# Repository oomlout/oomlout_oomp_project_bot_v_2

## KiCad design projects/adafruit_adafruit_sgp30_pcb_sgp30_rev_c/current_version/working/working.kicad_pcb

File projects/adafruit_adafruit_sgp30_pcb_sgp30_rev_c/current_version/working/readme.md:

# adafruit_sgp30_pcb
 
## summary 
* id: adafruit_adafruit_sgp30_pcb_sgp30_rev_c
* user: adafruit
* name: adafruit_sgp30_pcb
* board: sgp30_rev_c
* repo: https://github.com/adafruit/Adafruit-SGP30-PCB

* src_file_repo_sch: 
* src_file_repo_sch_link: https://github.com/adafruit/Adafruit-SGP30-PCB/tree/master/
* full details link: https://github.com/oomlout/oomlout_oomp_project_bot_v_2/tree/main/projects/adafruit_adafruit_sgp30_pcb_sgp30_rev_c/current_version/working  

## schematic  
  
[schematic (pdf)](working_schematic.pdf) 

## pcb  

[board (pdf)](working.pdf)  

## working_bom
| Id | Designator | Footprint | Quantity | Designation | Supplier and ref |  | None | 
| --- | --- | --- | --- | --- | --- | --- | --- | 
| 1 | FID4,FID3 | FIDUCIAL_1MM | 2 | FIDUCIAL_1MM |  |  | [''] | 
| 2 | CONN4,CONN3 | JST_SH4 | 2 | STEMMA_I2C_QT |  |  | [''] | 
| 3 | C5,C4 | 0805-NO | 2 | 10uF |  |  | [''] | 
| 4 | U1 | SOT23-5 | 1 | MIC5225-1.8V |  |  | [''] | 
| 5 | U$2 | SGP30 | 1 | SGP30 |  |  | [''] | 
| 6 | U$29,U$31,U$32,U$28 | MOUNTINGHOLE_2.5_PLATED | 4 | MOUNTINGHOLE2.5 |  |  | [''] | 
| 7 | D1 | CHIPLED_0603_NOOUTLINE | 1 | GREEN |  |  | [''] | 
| 8 | Q2 | SOT363 | 1 | BSS138 |  |  | [''] | 
| 9 | U$34 | ADAFRUIT_3.5MM | 1 |  |  |  | [''] | 
| 10 | C6 | 0603-NO | 1 | 0.1uF |  |  | [''] | 
| 11 | R3 | RESPACK_4X0603 | 1 | 10K |  |  | [''] | 
| 12 | JP3 | 1X05_ROUND_70 | 1 |  |  |  | [''] | 
| 13 | R2 | 0603-NO | 1 | 10K |  |  | [''] | 
| 14 | U$37,U$36 | STEMMAQT | 2 |  |  |  | [''] | 
| 15 | U$35 | PCBFEAT-REV-040 | 1 |  |  |  | [''] | 

## bom_schematic
| Ref | Qnty | Value | Cmp name | Footprint | Description | Vendor | DNP | 
| --- | --- | --- | --- | --- | --- | --- | --- | 
| C4, C5 | 2 | 10uF | CAP_CERAMIC0805-NOOUTLINE | working:0805-NO |  |  |  | 
| C6 | 1 | 0.1uF | CAP_CERAMIC0603_NO | working:0603-NO |  |  |  | 
| CONN3, CONN4 | 2 | STEMMA_I2C_QT | STEMMA_I2C_QT | working:JST_SH4 |  |  |  | 
| D1 | 1 | GREEN | LED0603_NOOUTLINE | working:CHIPLED_0603_NOOUTLINE |  |  |  | 
| FID3, FID4 | 2 | FIDUCIAL_1MM | FIDUCIAL_1MM | working:FIDUCIAL_1MM |  |  |  | 
| JP3 | 1 | HEADER-1X570MIL | HEADER-1X570MIL | working:1X05_ROUND_70 |  |  |  | 
| Q2 | 1 | BSS138 | MOSFET-N_DUAL | working:SOT363 |  |  |  | 
| R2 | 1 | 10K | RESISTOR_0603_NOOUT | working:0603-NO |  |  |  | 
| R3 | 1 | 10K | RESISTOR_4PACK | working:RESPACK_4X0603 |  |  |  | 
| U1 | 1 | MIC5225-1.8V | VREG_SOT23-5 | working:SOT23-5 |  |  |  | 
| U$2 | 1 | SGP30 | SGP30 | working:SGP30 |  |  |  | 
| U$28, U$29, U$31, U$32 | 4 | MOUNTINGHOLE2.5 | MOUNTINGHOLE2.5 | working:MOUNTINGHOLE_2.5_PLATED |  |  |  | 

## mounting_holes
| x | y | package | value | ref | size | 
| --- | --- | --- | --- | --- | --- | 
| 0.0 | 12.7 | MOUNTINGHOLE_2.5_PLATED | MOUNTINGHOLE2.5 | U$28 | m3 | 
| 20.32 | 12.7 | MOUNTINGHOLE_2.5_PLATED | MOUNTINGHOLE2.5 | U$29 | m3 | 
| 0.0 | 0.0 | MOUNTINGHOLE_2.5_PLATED | MOUNTINGHOLE2.5 | U$31 | m3 | 
| 20.32 | 0.0 | MOUNTINGHOLE_2.5_PLATED | MOUNTINGHOLE2.5 | U$32 | m3 |

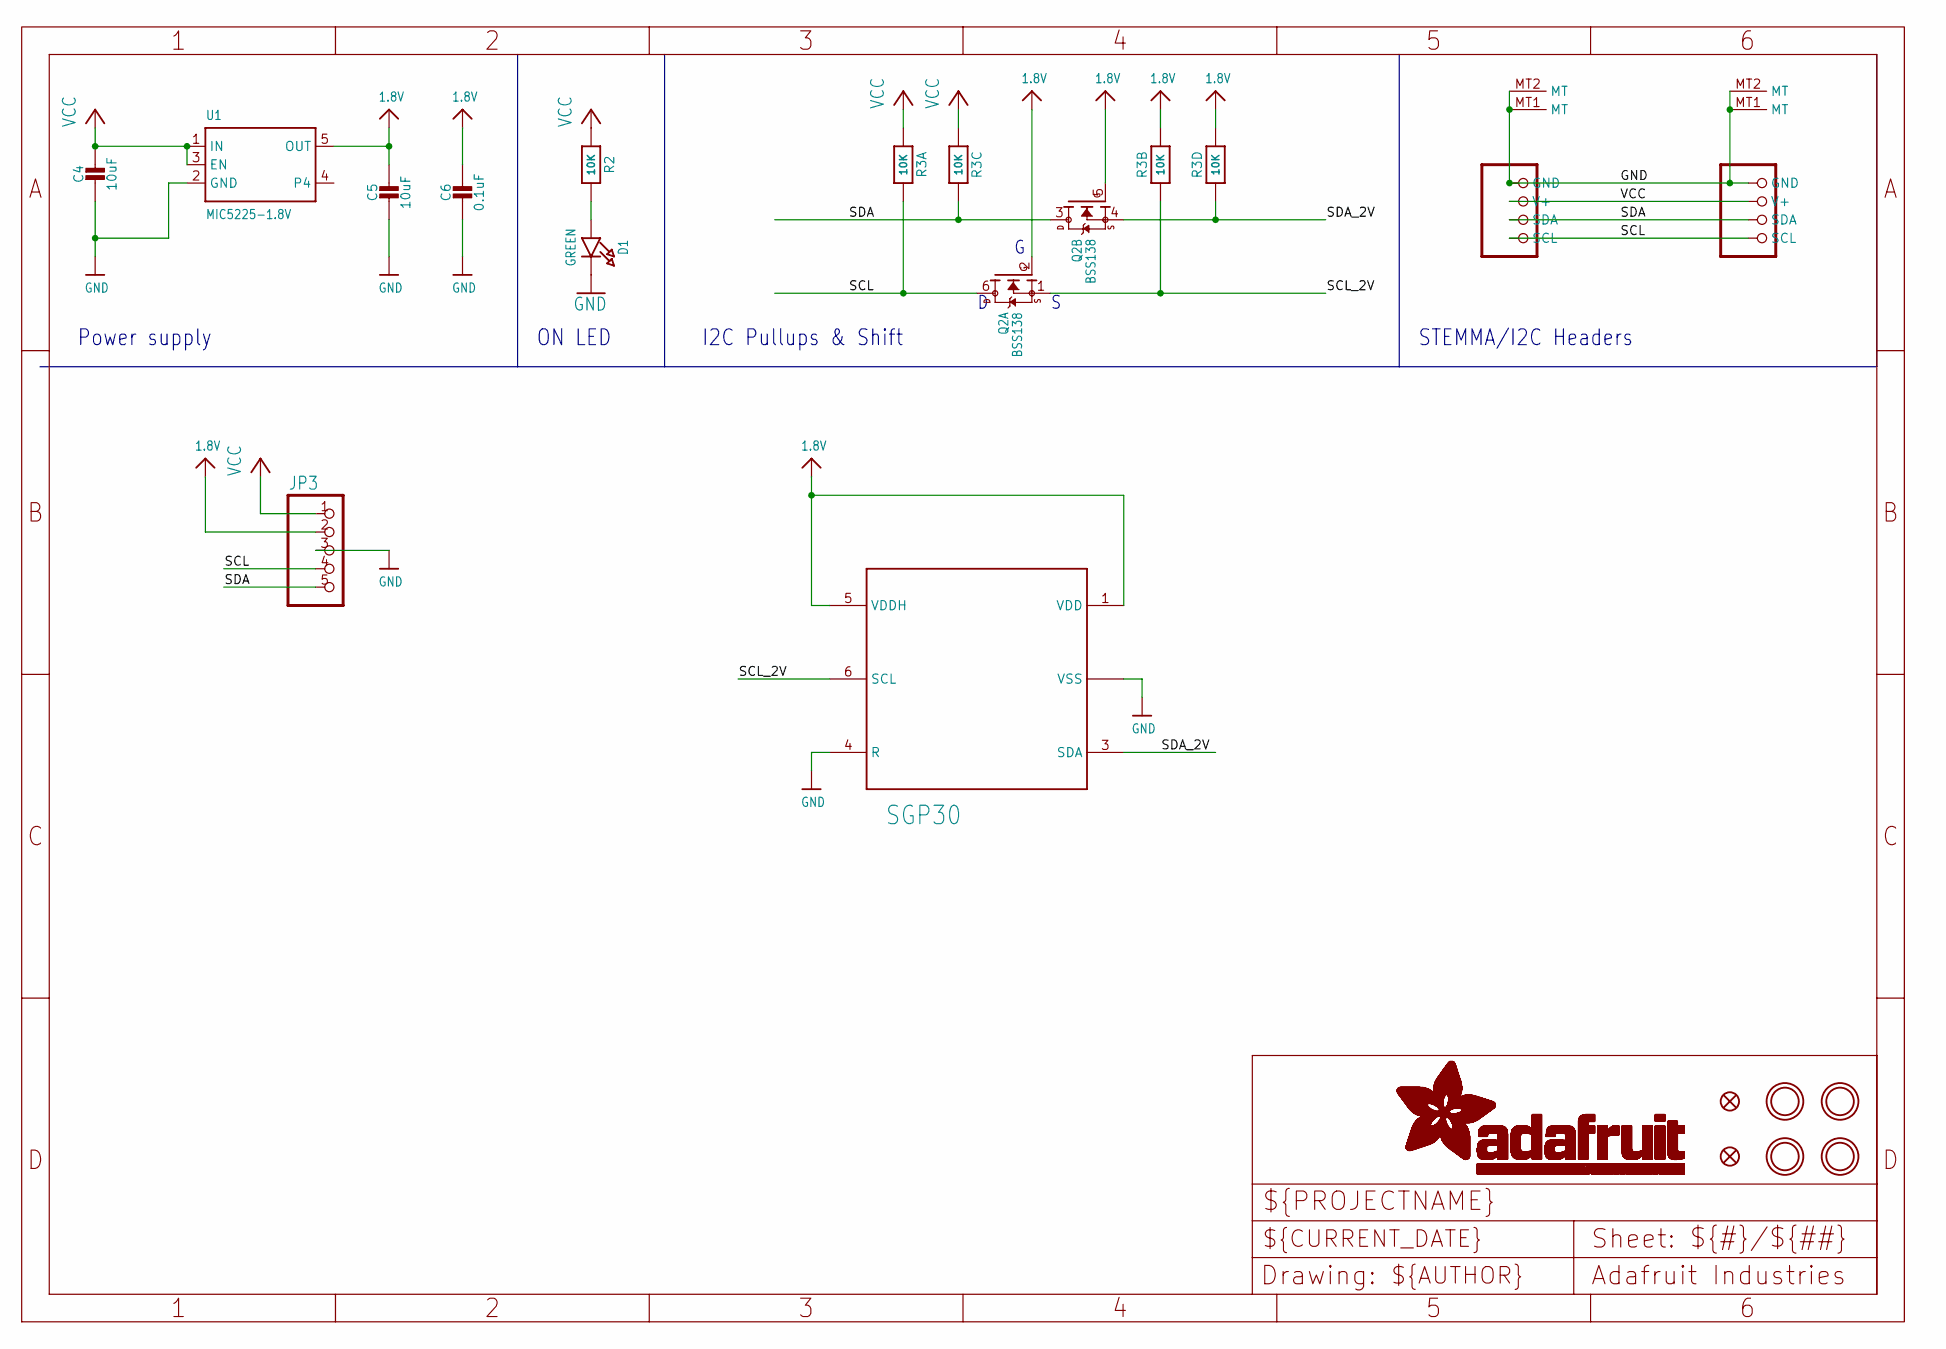
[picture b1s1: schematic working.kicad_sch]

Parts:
C4, C5: 10uF; 0805-NO
C6: 0.1uF; 0603-NO
CONN3, CONN4: STEMMA_I2C_QT; JST_SH4
D1: GREEN; CHIPLED_0603_NOOUTLINE
FID3, FID4: FIDUCIAL_1MM
JP3: HEADER-1X570MIL; 1X05_ROUND_70
Q2: BSS138; SOT363
R2: 10K; 0603-NO
R3: 10K; RESPACK_4X0603
U1: MIC5225-1.8V; SOT23-5
U$2: SGP30
U$28, U$29, U$31, U$32: MOUNTINGHOLE2.5; MOUNTINGHOLE_2.5_PLATED

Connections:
1.8V: C5.1, C6.1, JP3.2, Q2.2 (G), Q2.5 (G), R3.2 (1), R3.4 (1), U1.5 (OUT), U$2.1 (VDD), U$2.5 (VDDH)
GND: C4.2, C5.2, C6.2, CONN3.1 (GND), CONN3.MT1 (MT), CONN3.MT2 (MT), CONN4.1 (GND), CONN4.MT1 (MT), CONN4.MT2 (MT), D1.C, JP3.3, U1.2 (GND), U$2.2 (VSS), U$2.4 (R), U$2.P$7 (VSS)
unnamed: D1.A, R2.2
SCL: CONN3.4 (SCL), CONN4.4 (SCL), JP3.4, Q2.6 (D), R3.8 (2)
SCL_2V: Q2.1 (S), R3.7 (2), U$2.6 (SCL)
SDA: CONN3.3 (SDA), CONN4.3 (SDA), JP3.5, Q2.3 (D), R3.6 (2)
SDA_2V: Q2.4 (S), R3.5 (2), U$2.3 (SDA)
VCC: C4.1, CONN3.2 (V+), CONN4.2 (V+), JP3.1, R2.1, R3.1, R3.3 (1), U1.1 (IN), U1.3 (EN)

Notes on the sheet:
STEMMA/I2C Headers
ON LED
Power supply
I2C Pullups & Shift

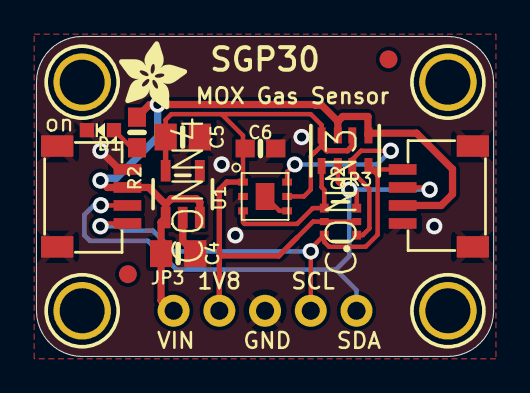
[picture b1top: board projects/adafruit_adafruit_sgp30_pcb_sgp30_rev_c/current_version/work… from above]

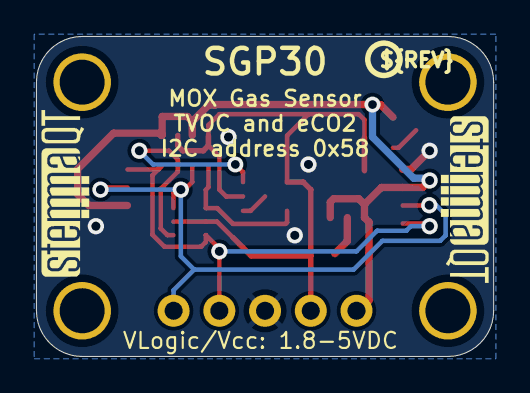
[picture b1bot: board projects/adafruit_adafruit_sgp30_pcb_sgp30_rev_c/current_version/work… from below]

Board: 2 copper layers, 25.4 x 17.8 mm, 22 parts (3 on the bottom side), 8 nets.

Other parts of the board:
U$34: ADAFRUIT_3.5MM
U$35: PCBFEAT-REV-040
U$36, U$37: STEMMAQT

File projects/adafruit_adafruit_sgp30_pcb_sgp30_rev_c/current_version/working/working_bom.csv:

"Id";"Designator";"Footprint";"Quantity";"Designation";"Supplier and ref";
1;"FID4,FID3";"FIDUCIAL_1MM";2;"FIDUCIAL_1MM";;;
2;"CONN4,CONN3";"JST_SH4";2;"STEMMA_I2C_QT";;;
3;"C5,C4";"0805-NO";2;"10uF";;;
4;"U1";"SOT23-5";1;"MIC5225-1.8V";;;
5;"U$2";"SGP30";1;"SGP30";;;
6;"U$29,U$31,U$32,U$28";"MOUNTINGHOLE_2.5_PLATED";4;"MOUNTINGHOLE2.5";;;
7;"D1";"CHIPLED_0603_NOOUTLINE";1;"GREEN";;;
8;"Q2";"SOT363";1;"BSS138";;;
9;"U$34";"ADAFRUIT_3.5MM";1;"";;;
10;"C6";"0603-NO";1;"0.1uF";;;
11;"R3";"RESPACK_4X0603";1;"10K";;;
12;"JP3";"1X05_ROUND_70";1;"";;;
13;"R2";"0603-NO";1;"10K";;;
14;"U$37,U$36";"STEMMAQT";2;"";;;
15;"U$35";"PCBFEAT-REV-040";1;"";;;

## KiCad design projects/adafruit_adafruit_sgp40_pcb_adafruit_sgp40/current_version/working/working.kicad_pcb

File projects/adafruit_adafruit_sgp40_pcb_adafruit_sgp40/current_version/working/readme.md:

# adafruit_sgp40_pcb
 
## summary 
* id: adafruit_adafruit_sgp40_pcb_adafruit_sgp40
* user: adafruit
* name: adafruit_sgp40_pcb
* board: adafruit_sgp40
* repo: https://github.com/adafruit/Adafruit-SGP40-PCB

* src_file_repo_sch: 
* src_file_repo_sch_link: https://github.com/adafruit/Adafruit-SGP40-PCB/tree/main/
* full details link: https://github.com/oomlout/oomlout_oomp_project_bot_v_2/tree/main/projects/adafruit_adafruit_sgp40_pcb_adafruit_sgp40/current_version/working  

## schematic  
  
[schematic (pdf)](working_schematic.pdf) 

## pcb  

[board (pdf)](working.pdf)  

## working_bom
| Id | Designator | Footprint | Quantity | Designation | Supplier and ref |  | None | 
| --- | --- | --- | --- | --- | --- | --- | --- | 
| 1 | D1 | CHIPLED_0603_NOOUTLINE | 1 | Green |  |  | [''] | 
| 2 | R3 | RESPACK_4X0603 | 1 | 10K |  |  | [''] | 
| 3 | R2 | 0603-NO | 1 | 10K |  |  | [''] | 
| 4 | CONN4,CONN3 | JST_SH4 | 2 | STEMMA_I2C_QT |  |  | [''] | 
| 5 | U$28,U$32,U$31,U$29 | MOUNTINGHOLE_2.5_PLATED | 4 | MOUNTINGHOLE2.5 |  |  | [''] | 
| 6 | U1 | SOT23-5 | 1 | AP2112-3.3K |  |  | [''] | 
| 7 | U$34 | ADAFRUIT_3.5MM | 1 |  |  |  | [''] | 
| 8 | Q2 | SOT363 | 1 | BSS138 |  |  | [''] | 
| 9 | JP3 | 1X05_ROUND_70 | 1 |  |  |  | [''] | 
| 10 | FID3,FID4 | FIDUCIAL_1MM | 2 | FIDUCIAL_1MM |  |  | [''] | 
| 11 | C6 | 0603-NO | 1 | 0.1uF |  |  | [''] | 
| 12 | C5,C4 | 0805-NO | 2 | 10uF |  |  | [''] | 
| 13 | X1 | SGP30 | 1 | SGP40 |  |  | [''] | 
| 14 | R1 | 0603-NO | 1 | 4.7ohm |  |  | [''] | 
| 15 | U$37,U$36 | STEMMAQT | 2 |  |  |  | [''] | 
| 16 | U$35 | PCBFEAT-REV-040 | 1 |  |  |  | [''] | 

## bom_schematic
| Ref | Qnty | Value | Cmp name | Footprint | Description | Vendor | DNP | 
| --- | --- | --- | --- | --- | --- | --- | --- | 
| C4, C5 | 2 | 10uF | CAP_CERAMIC0805-NOOUTLINE | working:0805-NO |  |  |  | 
| C6 | 1 | 0.1uF | CAP_CERAMIC0603_NO | working:0603-NO |  |  |  | 
| CONN3, CONN4 | 2 | STEMMA_I2C_QT | STEMMA_I2C_QT | working:JST_SH4 |  |  |  | 
| D1 | 1 | Green | LED0603_NOOUTLINE | working:CHIPLED_0603_NOOUTLINE |  |  |  | 
| FID3, FID4 | 2 | FIDUCIAL_1MM | FIDUCIAL_1MM | working:FIDUCIAL_1MM |  |  |  | 
| JP3 | 1 | HEADER-1X570MIL | HEADER-1X570MIL | working:1X05_ROUND_70 |  |  |  | 
| Q2 | 1 | BSS138 | MOSFET-N_DUAL | working:SOT363 |  |  |  | 
| R1 | 1 | 4.7ohm | RESISTOR_0603_NOOUT | working:0603-NO |  |  |  | 
| R2 | 1 | 10K | RESISTOR_0603_NOOUT | working:0603-NO |  |  |  | 
| R3 | 1 | 10K | RESISTOR_4PACK | working:RESPACK_4X0603 |  |  |  | 
| U1 | 1 | AP2112-3.3K | VREG_SOT23-5 | working:SOT23-5 |  |  |  | 
| U$28, U$29, U$31, U$32 | 4 | MOUNTINGHOLE2.5 | MOUNTINGHOLE2.5 | working:MOUNTINGHOLE_2.5_PLATED |  |  |  | 
| X1 | 1 | SGP30 | SGP30 | working:SGP30 |  |  |  | 

## mounting_holes
| x | y | package | value | ref | size | 
| --- | --- | --- | --- | --- | --- | 
| 0.0 | 12.7 | MOUNTINGHOLE_2.5_PLATED | MOUNTINGHOLE2.5 | U$28 | m3 | 
| 20.32 | 12.7 | MOUNTINGHOLE_2.5_PLATED | MOUNTINGHOLE2.5 | U$29 | m3 | 
| 0.0 | 0.0 | MOUNTINGHOLE_2.5_PLATED | MOUNTINGHOLE2.5 | U$31 | m3 | 
| 20.32 | 0.0 | MOUNTINGHOLE_2.5_PLATED | MOUNTINGHOLE2.5 | U$32 | m3 |

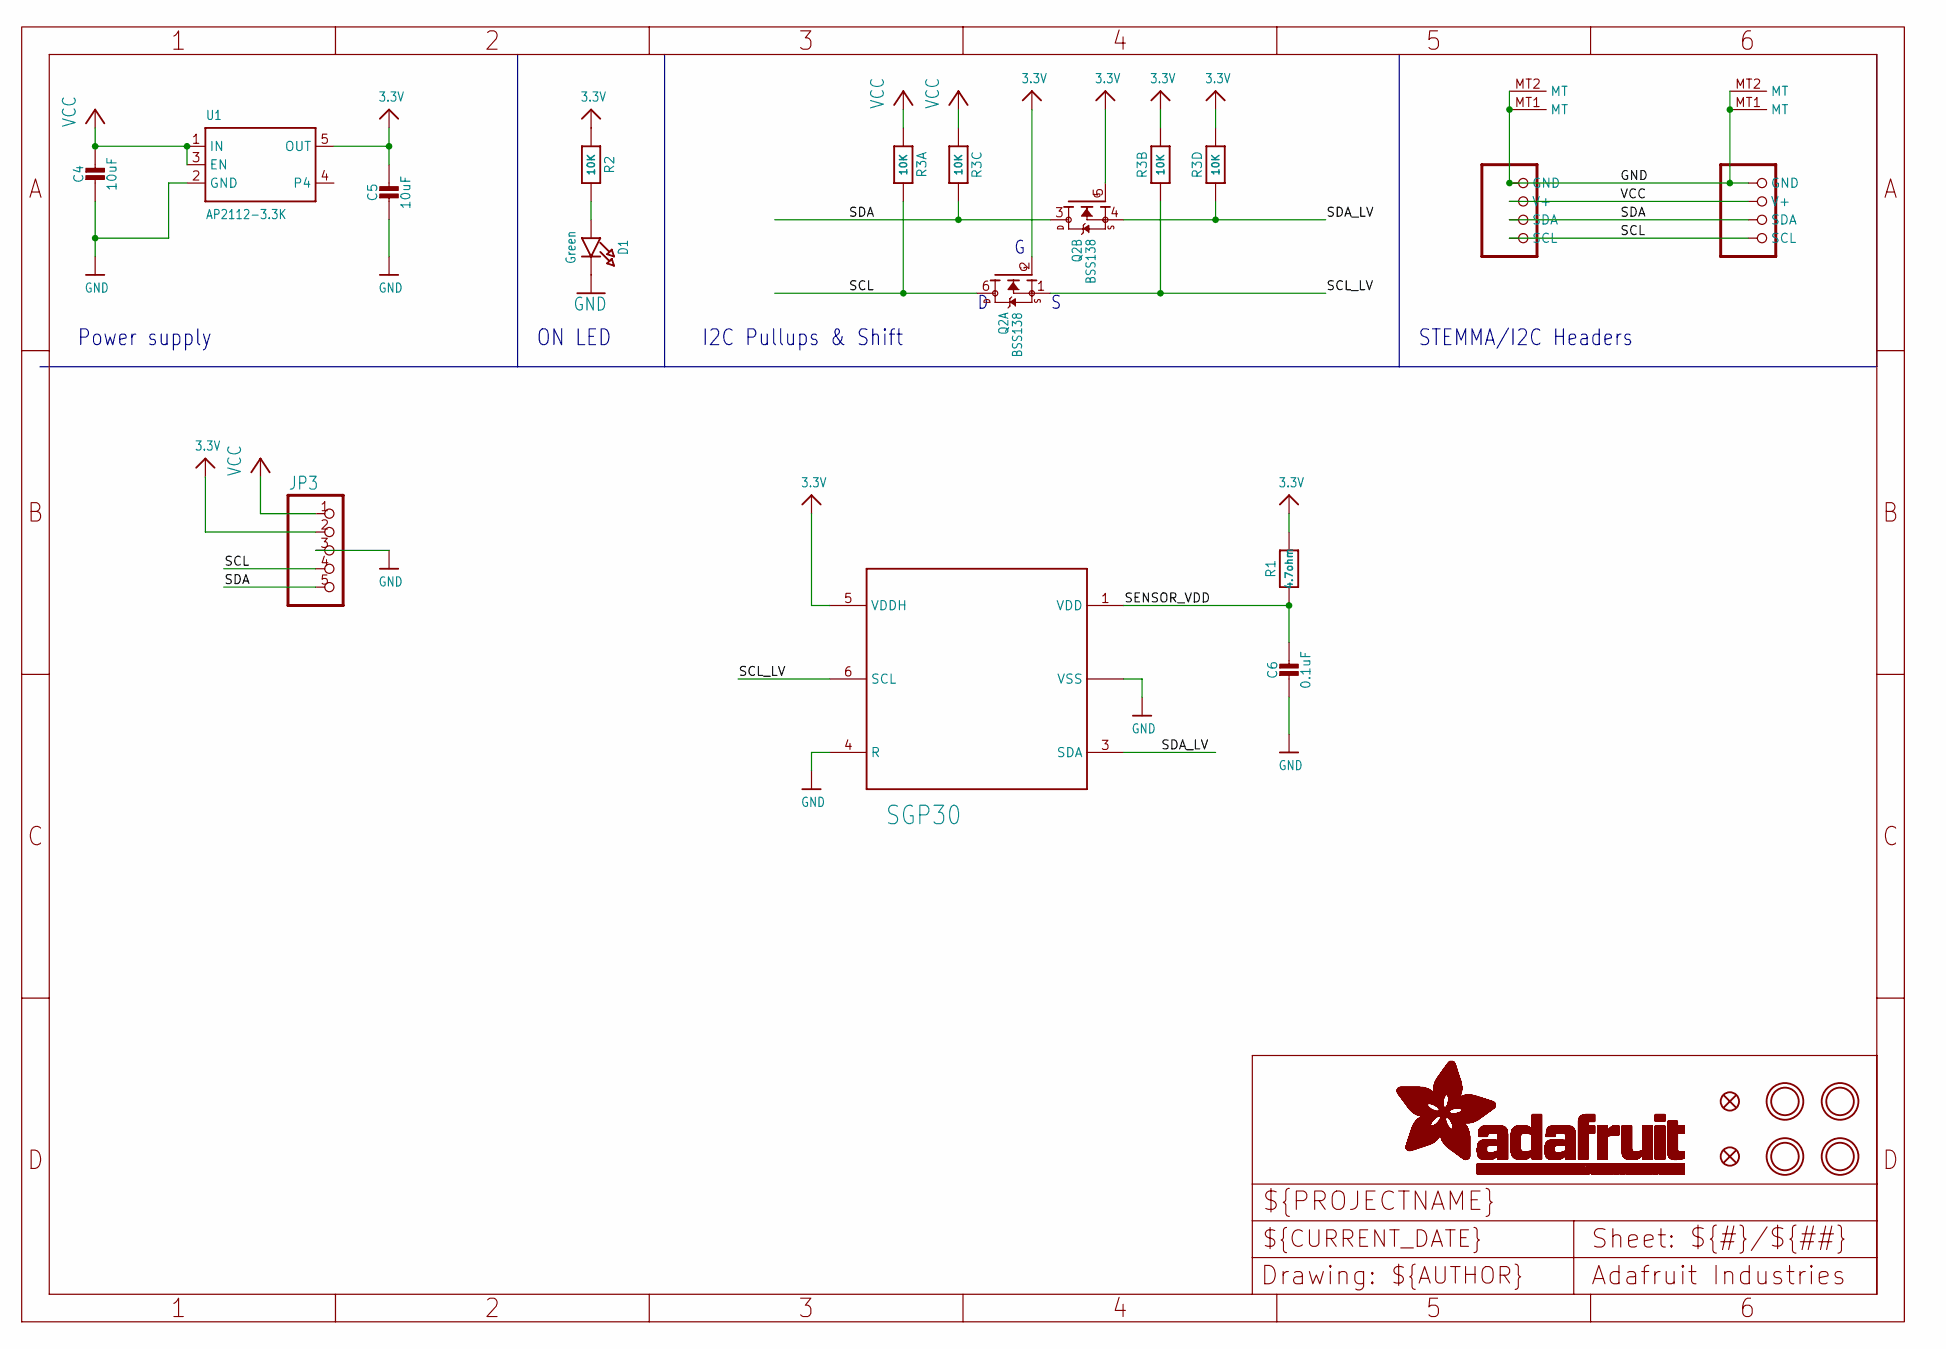
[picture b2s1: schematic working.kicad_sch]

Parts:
C4, C5: 10uF; 0805-NO
C6: 0.1uF; 0603-NO
CONN3, CONN4: STEMMA_I2C_QT; JST_SH4
D1: Green; CHIPLED_0603_NOOUTLINE
FID3, FID4: FIDUCIAL_1MM
JP3: HEADER-1X570MIL; 1X05_ROUND_70
Q2: BSS138; SOT363
R1: 4.7ohm; 0603-NO
R2: 10K; 0603-NO
R3: 10K; RESPACK_4X0603
U1: AP2112-3.3K; SOT23-5
U$28, U$29, U$31, U$32: MOUNTINGHOLE2.5; MOUNTINGHOLE_2.5_PLATED
X1: SGP30

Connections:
3.3V: C5.1, JP3.2, Q2.2 (G), Q2.5 (G), R1.2, R2.1, R3.2 (1), R3.4 (1), U1.5 (OUT), X1.5 (VDDH)
GND: C4.2, C5.2, C6.2, CONN3.1 (GND), CONN3.MT1 (MT), CONN3.MT2 (MT), CONN4.1 (GND), CONN4.MT1 (MT), CONN4.MT2 (MT), D1.C, JP3.3, U1.2 (GND), X1.2 (VSS), X1.4 (R), X1.P$7 (VSS)
unnamed: D1.A, R2.2
SCL: CONN3.4 (SCL), CONN4.4 (SCL), JP3.4, Q2.6 (D), R3.8 (2)
SCL_LV: Q2.1 (S), R3.7 (2), X1.6 (SCL)
SDA: CONN3.3 (SDA), CONN4.3 (SDA), JP3.5, Q2.3 (D), R3.6 (2)
SDA_LV: Q2.4 (S), R3.5 (2), X1.3 (SDA)
SENSOR_VDD: C6.1, R1.1, X1.1 (VDD)
VCC: C4.1, CONN3.2 (V+), CONN4.2 (V+), JP3.1, R3.1, R3.3 (1), U1.1 (IN), U1.3 (EN)

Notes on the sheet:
STEMMA/I2C Headers
I2C Pullups & Shift
ON LED
Power supply

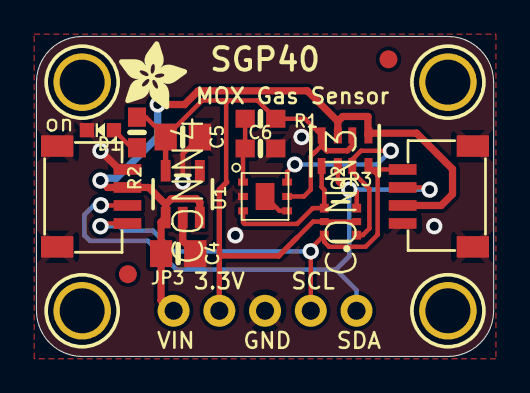
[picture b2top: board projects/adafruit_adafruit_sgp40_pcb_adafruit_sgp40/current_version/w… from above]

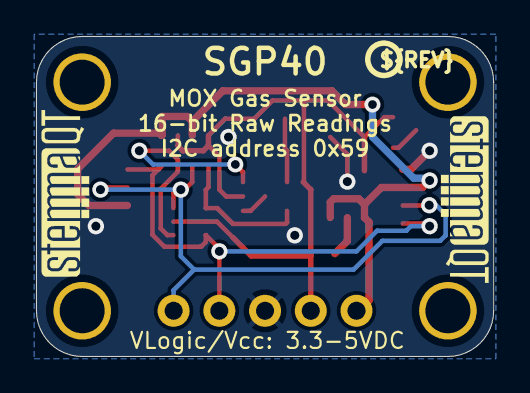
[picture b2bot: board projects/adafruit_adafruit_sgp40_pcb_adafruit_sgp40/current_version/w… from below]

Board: 2 copper layers, 25.4 x 17.8 mm, 23 parts (3 on the bottom side), 9 nets.

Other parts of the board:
U$34: ADAFRUIT_3.5MM
U$35: PCBFEAT-REV-040
U$36, U$37: STEMMAQT

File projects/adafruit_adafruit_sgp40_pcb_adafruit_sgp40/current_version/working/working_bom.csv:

"Id";"Designator";"Footprint";"Quantity";"Designation";"Supplier and ref";
1;"D1";"CHIPLED_0603_NOOUTLINE";1;"Green";;;
2;"R3";"RESPACK_4X0603";1;"10K";;;
3;"R2";"0603-NO";1;"10K";;;
4;"CONN4,CONN3";"JST_SH4";2;"STEMMA_I2C_QT";;;
5;"U$28,U$32,U$31,U$29";"MOUNTINGHOLE_2.5_PLATED";4;"MOUNTINGHOLE2.5";;;
6;"U1";"SOT23-5";1;"AP2112-3.3K";;;
7;"U$34";"ADAFRUIT_3.5MM";1;"";;;
8;"Q2";"SOT363";1;"BSS138";;;
9;"JP3";"1X05_ROUND_70";1;"";;;
10;"FID3,FID4";"FIDUCIAL_1MM";2;"FIDUCIAL_1MM";;;
11;"C6";"0603-NO";1;"0.1uF";;;
12;"C5,C4";"0805-NO";2;"10uF";;;
13;"X1";"SGP30";1;"SGP40";;;
14;"R1";"0603-NO";1;"4.7ohm";;;
15;"U$37,U$36";"STEMMAQT";2;"";;;
16;"U$35";"PCBFEAT-REV-040";1;"";;;

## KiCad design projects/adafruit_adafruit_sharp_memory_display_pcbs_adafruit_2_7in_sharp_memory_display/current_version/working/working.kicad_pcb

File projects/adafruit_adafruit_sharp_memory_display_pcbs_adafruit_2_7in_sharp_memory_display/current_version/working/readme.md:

# adafruit_sharp_memory_display_pcbs
 
## summary 
* id: adafruit_adafruit_sharp_memory_display_pcbs_adafruit_2_7in_sharp_memory_display
* user: adafruit
* name: adafruit_sharp_memory_display_pcbs
* board: adafruit_2_7in_sharp_memory_display
* repo: https://github.com/adafruit/Adafruit-Sharp-Memory-Display-PCBs

* src_file_repo_sch: 
* src_file_repo_sch_link: https://github.com/adafruit/Adafruit-Sharp-Memory-Display-PCBs/tree/master/
* full details link: https://github.com/oomlout/oomlout_oomp_project_bot_v_2/tree/main/projects/adafruit_adafruit_sharp_memory_display_pcbs_adafruit_2_7in_sharp_memory_display/current_version/working  

## schematic  
  
[schematic (pdf)](working_schematic.pdf) 

## pcb  

[board (pdf)](working.pdf)  

## working_bom
| Id | Designator | Footprint | Quantity | Designation | Supplier and ref |  | None | 
| --- | --- | --- | --- | --- | --- | --- | --- | 
| 1 | FID1,FID3,FID2 | FIDUCIAL_1MM | 3 | FIDUCIAL_1MM |  |  | [''] | 
| 2 | JP1 | 1X09_ROUND_70 | 1 |  |  |  | [''] | 
| 3 | R2,R1,R3 | 0603-NO | 3 | 10K |  |  | [''] | 
| 4 | C3 | 0805-NO | 1 | 1ÂµF |  |  | [''] | 
| 5 | C8 | 0805-NO | 1 | 1uF |  |  | [''] | 
| 6 | C6,C7 | 0805-NO | 2 | 10uF |  |  | [''] | 
| 7 | C2 | 0805_10MGAP | 1 | 1ÂµF |  |  | [''] | 
| 8 | U$29 | PCBFEAT-REV-040 | 1 |  |  |  | [''] | 
| 9 | C5,C4 | 0805-NO | 2 | 10ÂµF |  |  | [''] | 
| 10 | FB1,FB2 | _0805 | 2 | FERRITE |  |  | [''] | 
| 11 | U2 | SOT23-5 | 1 | AP2112K-3.3 |  |  | [''] | 
| 12 | U$32 | ADAFRUIT_TEXT_20MM | 1 |  |  |  | [''] | 
| 13 | IC1 | SHARP_2.7IN | 1 | LS013B4DN04 |  |  | [''] | 
| 14 | U$22,U$21 | MOUNTINGHOLE_2.5_PLATED_THICK | 2 | MOUNTINGHOLE2.5_THICK |  |  | [''] | 
| 15 | C1 | 0603-NO | 1 | 0.1ÂµF |  |  | [''] | 
| 16 | U$27,U$28 | MOUNTINGHOLE_2.5_PLATED | 2 | MOUNTINGHOLE2.5 |  |  | [''] | 
| 17 | IC2 | SOT23-6 | 1 | AP3602 |  |  | [''] | 
| 18 | U1 | SOIC16 | 1 | 74HC4050D |  |  | [''] | 

## bom_schematic
| Ref | Qnty | Value | Cmp name | Footprint | Description | Vendor | DNP | 
| --- | --- | --- | --- | --- | --- | --- | --- | 
| C1 | 1 | 0.1ÂµF | CAP_CERAMIC0603_NO | working:0603-NO |  |  |  | 
| C2 | 1 | 1ÂµF | CAP_CERAMIC0805_10MGAP | working:0805_10MGAP |  |  |  | 
| C3 | 1 | 1ÂµF | CAP_CERAMIC0805-NOOUTLINE | working:0805-NO |  |  |  | 
| C4, C5 | 2 | 10ÂµF | CAP_CERAMIC0805-NOOUTLINE | working:0805-NO |  |  |  | 
| C6, C7 | 2 | 10uF | CAP_CERAMIC0805-NOOUTLINE | working:0805-NO |  |  |  | 
| C8 | 1 | 1uF | CAP_CERAMIC0805-NOOUTLINE | working:0805-NO |  |  |  | 
| FB1, FB2 | 2 | FERRITE | FERRITE_0805 | working:_0805 |  |  |  | 
| FID1, FID2, FID3 | 3 | FIDUCIAL_1MM | FIDUCIAL_1MM | working:FIDUCIAL_1MM |  |  |  | 
| IC1 | 1 | LS013B4DN04 | DISP_EINK_SHARPMEMORYLCD_10PIN_27IN | working:SHARP_2.7IN |  |  |  | 
| IC2 | 1 | AP3602 | AP3602 | working:SOT23-6 |  |  |  | 
| JP1 | 1 | HEADER-1X970MIL | HEADER-1X970MIL | working:1X09_ROUND_70 |  |  |  | 
| R1, R2, R3 | 3 | 10K | RESISTOR_0603_NOOUT | working:0603-NO |  |  |  | 
| U1 | 1 | 74HC4050D | 74HC4050D | working:SOIC16 |  |  |  | 
| U2 | 1 | AP2112K-3.3 | VREG_SOT23-5 | working:SOT23-5 |  |  |  | 
| U$21, U$22 | 2 | MOUNTINGHOLE2.5_THICK | MOUNTINGHOLE2.5_THICK | working:MOUNTINGHOLE_2.5_PLATED_THICK |  |  |  | 
| U$27, U$28 | 2 | MOUNTINGHOLE2.5 | MOUNTINGHOLE2.5 | working:MOUNTINGHOLE_2.5_PLATED |  |  |  | 

## mounting_holes
| x | y | package | value | ref | size | 
| --- | --- | --- | --- | --- | --- | 
| 58.42 | 0.0 | MOUNTINGHOLE_2.5_PLATED_THICK | MOUNTINGHOLE2.5_THICK | U$21 | m3 | 
| 0.0 | 0.0 | MOUNTINGHOLE_2.5_PLATED_THICK | MOUNTINGHOLE2.5_THICK | U$22 | m3 | 
| 58.42 | 50.8 | MOUNTINGHOLE_2.5_PLATED | MOUNTINGHOLE2.5 | U$27 | m3 | 
| 0.0 | 50.8 | MOUNTINGHOLE_2.5_PLATED | MOUNTINGHOLE2.5 | U$28 | m3 |

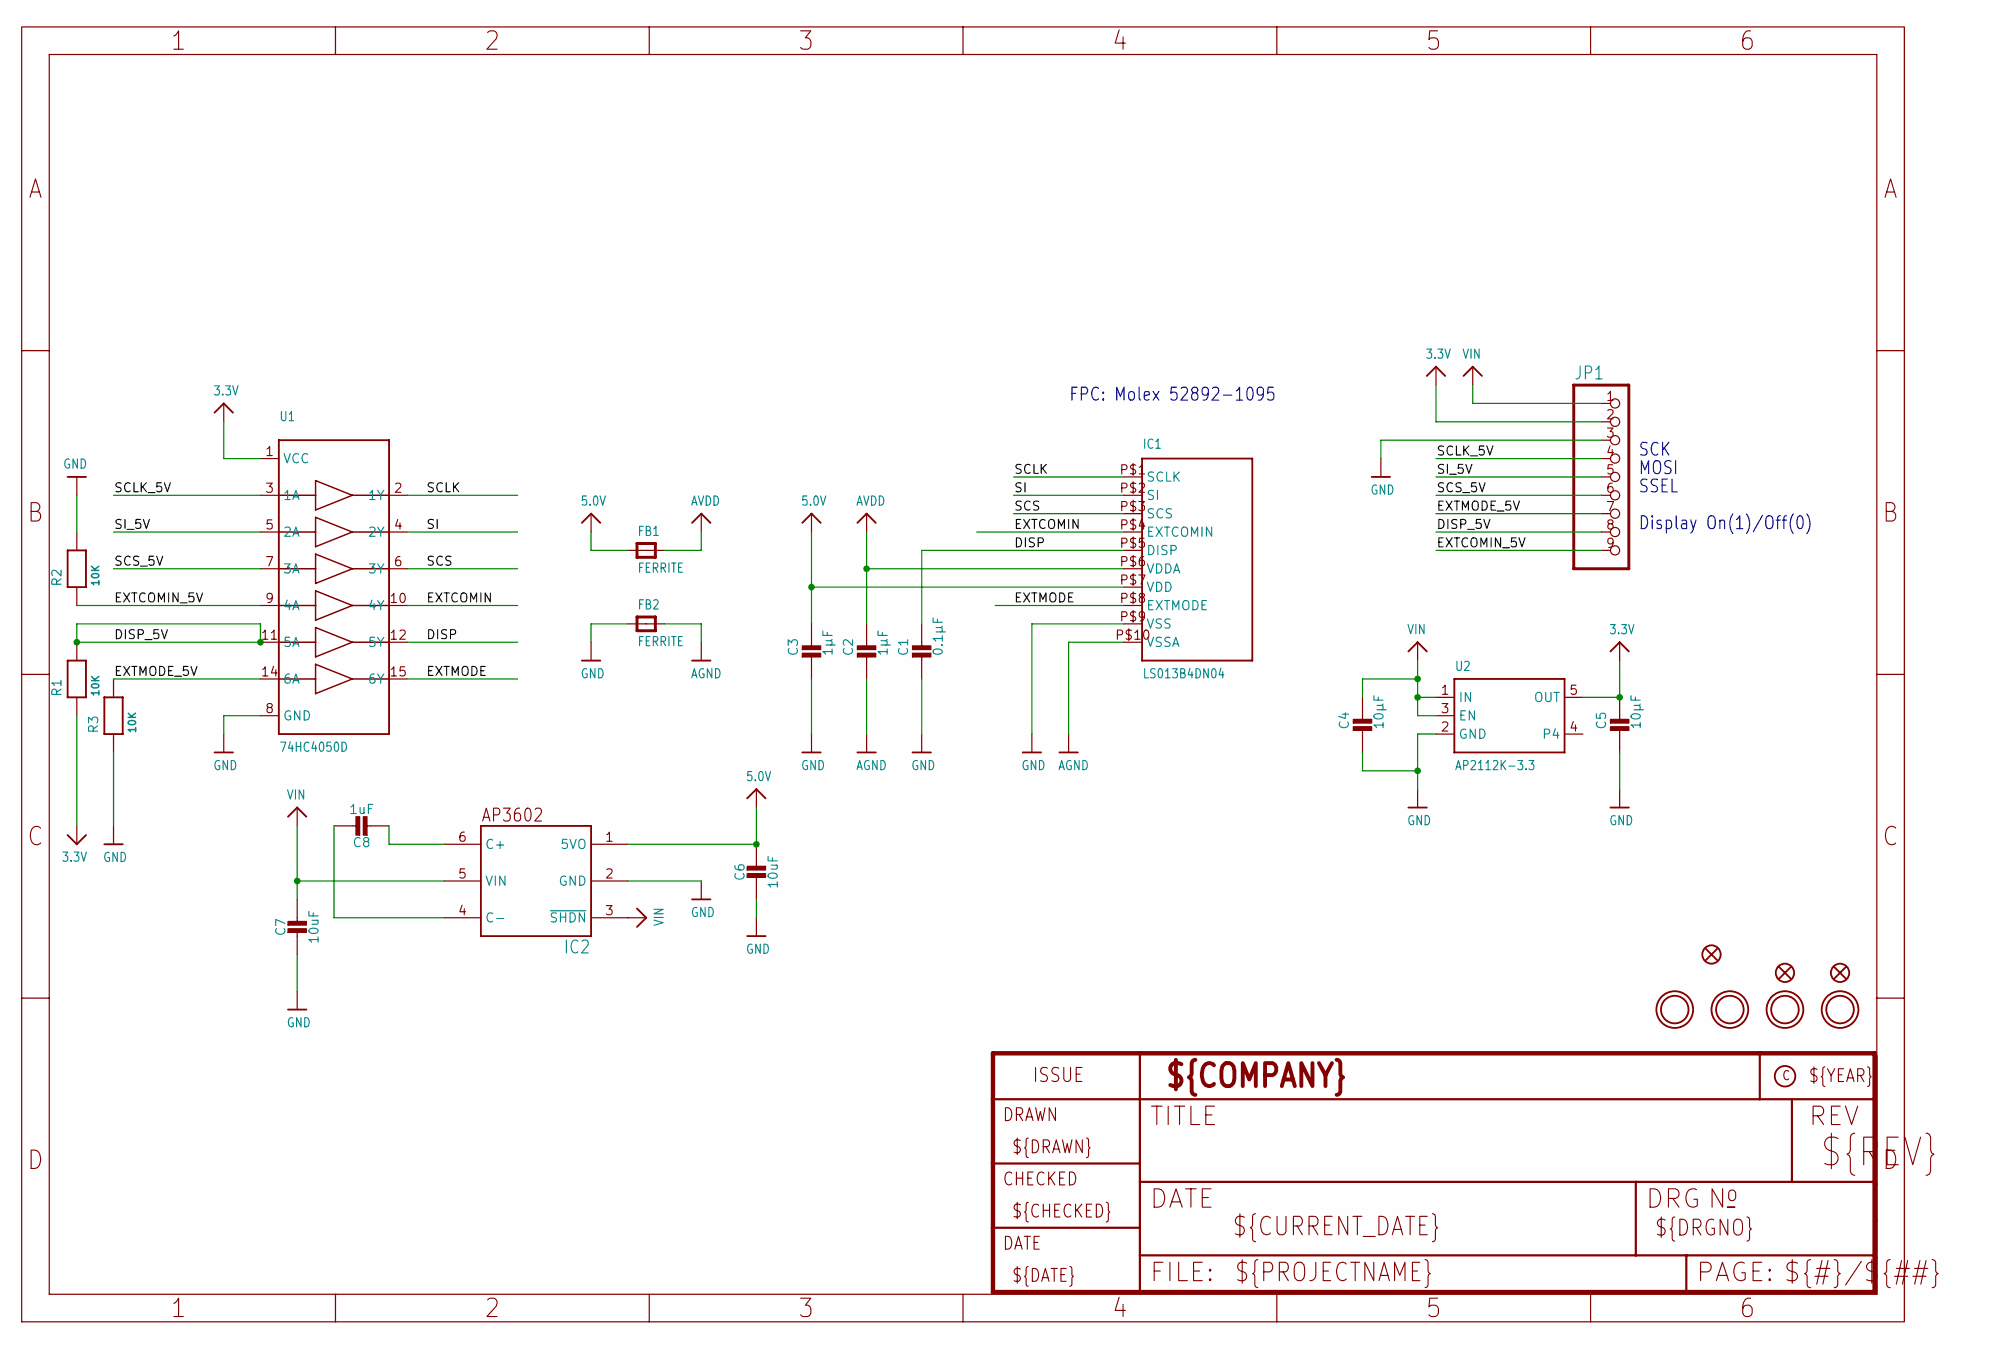
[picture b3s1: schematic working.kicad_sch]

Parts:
C1: 0.1µF; 0603-NO
C2: 1µF; 0805_10MGAP
C3: 1µF; 0805-NO
C4, C5: 10µF; 0805-NO
C6, C7: 10uF; 0805-NO
C8: 1uF; 0805-NO
FB1, FB2: FERRITE; _0805
FID1, FID2, FID3: FIDUCIAL_1MM
IC1: LS013B4DN04; SHARP_2.7IN
IC2: AP3602; SOT23-6
JP1: HEADER-1X970MIL; 1X09_ROUND_70
R1, R2, R3: 10K; 0603-NO
U1: 74HC4050D; SOIC16
U2: AP2112K-3.3; SOT23-5
U$21, U$22: MOUNTINGHOLE2.5_THICK; MOUNTINGHOLE_2.5_PLATED_THICK
U$27, U$28: MOUNTINGHOLE2.5; MOUNTINGHOLE_2.5_PLATED

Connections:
3.3V: C5.1, JP1.2, R1.1, U1.1 (VCC), U2.5 (OUT)
5.0V: C3.1, C6.1, FB1.1, IC1.P$7 (VDD), IC2.1 (5VO)
AGND: C2.2, FB2.2, IC1.P$10 (VSSA)
AVDD: C2.1, FB1.2, IC1.P$6 (VDDA)
DISP: C1.1, IC1.P$5 (DISP), U1.12 (5Y)
DISP_5V: JP1.8, R1.2, U1.11 (5A)
EXTCOMIN: IC1.P$4 (EXTCOMIN), U1.10 (4Y)
EXTCOMIN_5V: JP1.9, R2.1, U1.9 (4A)
EXTMODE: IC1.P$8 (EXTMODE), U1.15 (6Y)
EXTMODE_5V: JP1.7, R3.2, U1.14 (6A)
GND: C1.2, C3.2, C4.2, C5.2, C6.2, C7.2, FB2.1, IC1.P$9 (VSS), IC2.2 (GND), JP1.3, R2.2, R3.1, U1.8 (GND), U2.2 (GND)
unnamed: C8.2, IC2.6 (C+)
unnamed: C8.1, IC2.4 (C-)
SCLK: IC1.P$1 (SCLK), U1.2 (1Y)
SCLK_5V: JP1.4, U1.3 (1A)
SCS: IC1.P$3 (SCS), U1.6 (3Y)
SCS_5V: JP1.6, U1.7 (3A)
SI: IC1.P$2 (SI), U1.4 (2Y)
SI_5V: JP1.5, U1.5 (2A)
VIN: C4.1, C7.1, IC2.3 (~SHDN), IC2.5 (VIN), JP1.1, U2.1 (IN), U2.3 (EN)

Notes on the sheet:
SSEL
MOSI
FPC: Molex 52892-1095
Display On(1)/Off(0)
SCK

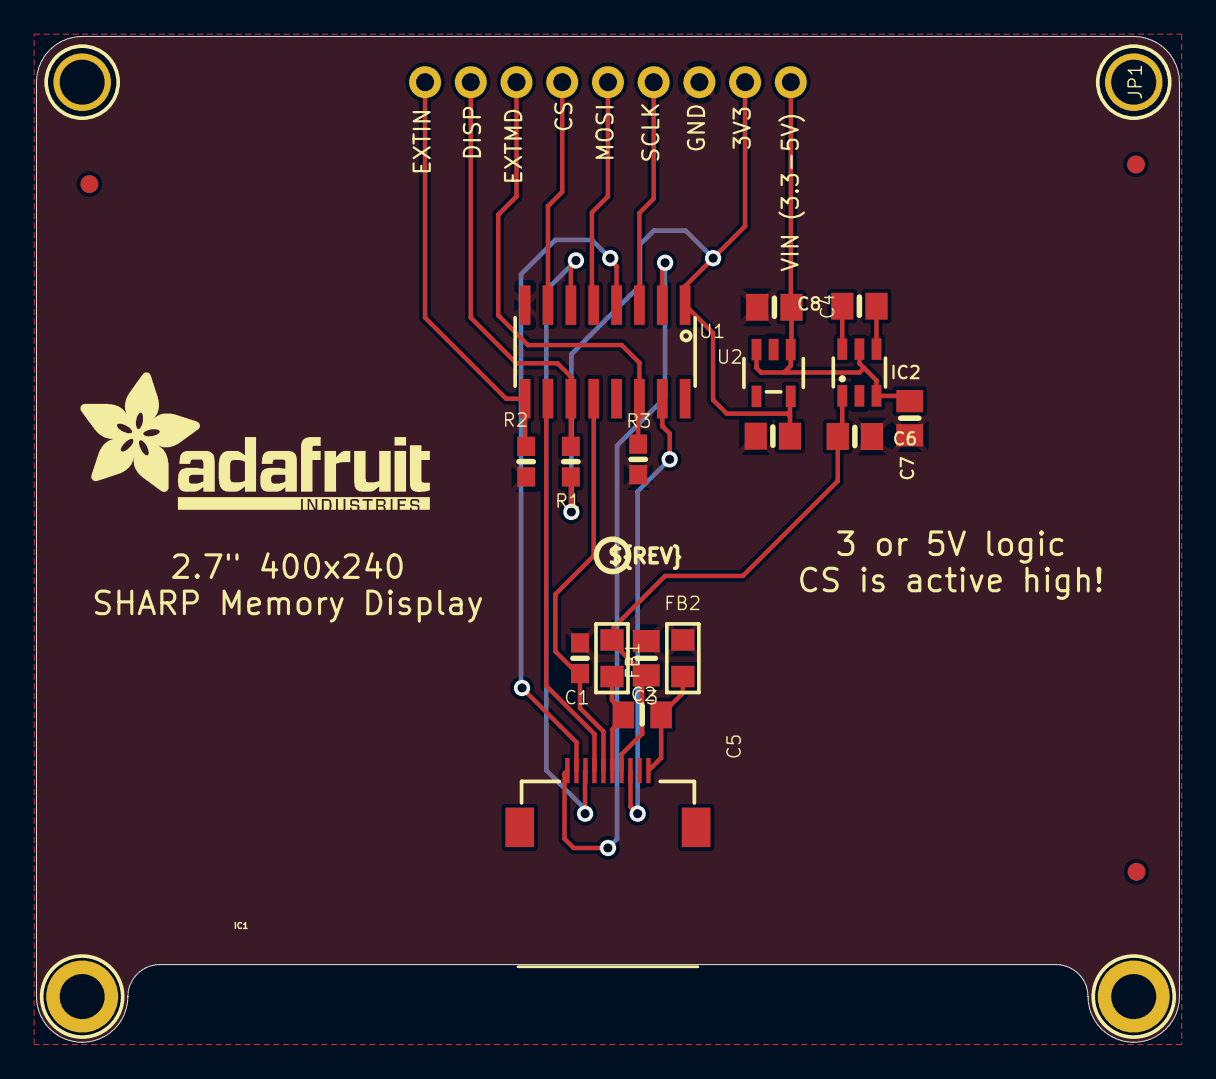
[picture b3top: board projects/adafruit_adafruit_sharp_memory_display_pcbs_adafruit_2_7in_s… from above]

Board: 16 copper layers, 63.5 x 55.9 mm, 27 parts (0 on the bottom side), 20 nets.

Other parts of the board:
U$29: PCBFEAT-REV-040
U$32: ADAFRUIT_TEXT_20MM

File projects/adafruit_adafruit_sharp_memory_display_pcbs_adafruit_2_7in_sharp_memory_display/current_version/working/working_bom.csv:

"Id";"Designator";"Footprint";"Quantity";"Designation";"Supplier and ref";
1;"FID1,FID3,FID2";"FIDUCIAL_1MM";3;"FIDUCIAL_1MM";;;
2;"JP1";"1X09_ROUND_70";1;"";;;
3;"R2,R1,R3";"0603-NO";3;"10K";;;
4;"C3";"0805-NO";1;"1µF";;;
5;"C8";"0805-NO";1;"1uF";;;
6;"C6,C7";"0805-NO";2;"10uF";;;
7;"C2";"0805_10MGAP";1;"1µF";;;
8;"U$29";"PCBFEAT-REV-040";1;"";;;
9;"C5,C4";"0805-NO";2;"10µF";;;
10;"FB1,FB2";"_0805";2;"FERRITE";;;
11;"U2";"SOT23-5";1;"AP2112K-3.3";;;
12;"U$32";"ADAFRUIT_TEXT_20MM";1;"";;;
13;"IC1";"SHARP_2.7IN";1;"LS013B4DN04";;;
14;"U$22,U$21";"MOUNTINGHOLE_2.5_PLATED_THICK";2;"MOUNTINGHOLE2.5_THICK";;;
15;"C1";"0603-NO";1;"0.1µF";;;
16;"U$27,U$28";"MOUNTINGHOLE_2.5_PLATED";2;"MOUNTINGHOLE2.5";;;
17;"IC2";"SOT23-6";1;"AP3602";;;
18;"U1";"SOIC16";1;"74HC4050D";;;

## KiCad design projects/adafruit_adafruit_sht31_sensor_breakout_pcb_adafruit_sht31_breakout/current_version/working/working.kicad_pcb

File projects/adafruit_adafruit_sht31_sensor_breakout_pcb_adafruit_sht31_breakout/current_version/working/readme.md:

# adafruit_sht31_sensor_breakout_pcb
 
## summary 
* id: adafruit_adafruit_sht31_sensor_breakout_pcb_adafruit_sht31_breakout
* user: adafruit
* name: adafruit_sht31_sensor_breakout_pcb
* board: adafruit_sht31_breakout
* repo: https://github.com/adafruit/Adafruit-SHT31-Sensor-Breakout-PCB

* src_file_repo_sch: 
* src_file_repo_sch_link: https://github.com/adafruit/Adafruit-SHT31-Sensor-Breakout-PCB/tree/master/
* full details link: https://github.com/oomlout/oomlout_oomp_project_bot_v_2/tree/main/projects/adafruit_adafruit_sht31_sensor_breakout_pcb_adafruit_sht31_breakout/current_version/working  

## schematic  
  
[schematic (pdf)](working_schematic.pdf) 

## pcb  

[board (pdf)](working.pdf)  

## working_bom
| Id | Designator | Footprint | Quantity | Designation | Supplier and ref |  | None | 
| --- | --- | --- | --- | --- | --- | --- | --- | 
| 1 | FID2,FID3 | FIDUCIAL_1MM | 2 | FIDUCIAL" |  |  | [''] | 
| 2 | U$1,U$2 | MOUNTINGHOLE_2.5_PLATED | 2 | MOUNTINGHOLE2.5 |  |  | [''] | 
| 3 | JP2 | 1X07_ROUND_70 | 1 |  |  |  | [''] | 
| 4 | C1 | 0805-NO | 1 | 10uF |  |  | [''] | 
| 5 | R1,R4,R2 | 0805-NO | 3 | 10K |  |  | [''] | 
| 6 | R3 | _0805MP | 1 | 10K |  |  | [''] | 
| 7 | U1 | SHT3X | 1 | SHT31-DIS |  |  | [''] | 
| 8 | U$13 | ADAFRUIT_2.5MM | 1 |  |  |  | [''] | 
| 9 | U$11 | PCBFEAT-REV-040 | 1 |  |  |  | [''] | 

## bom_schematic
| Ref | Qnty | Value | Cmp name | Footprint | Description | Vendor | DNP | 
| --- | --- | --- | --- | --- | --- | --- | --- | 
| C1 | 1 | 10uF | CAP_CERAMIC0805-NOOUTLINE | working:0805-NO |  |  |  | 
| FID2, FID3 | 2 | FIDUCIAL"" | FIDUCIAL{dblquote}{dblquote} | working:FIDUCIAL_1MM |  |  |  | 
| JP2 | 1 | HEADER-1X770MIL | HEADER-1X770MIL | working:1X07_ROUND_70 |  |  |  | 
| R1, R2, R4 | 3 | 10K | RESISTOR0805_NOOUTLINE | working:0805-NO |  |  |  | 
| R3 | 1 | 10K | RESISTOR_0805MP | working:_0805MP |  |  |  | 
| U1 | 1 | SHT31-DIS | SHT3X | working:SHT3X |  |  |  | 
| U$1, U$2 | 2 | MOUNTINGHOLE2.5 | MOUNTINGHOLE2.5 | working:MOUNTINGHOLE_2.5_PLATED |  |  |  | 

## mounting_holes
| x | y | package | value | ref | size | 
| --- | --- | --- | --- | --- | --- | 
| 0.0 | 0.0 | MOUNTINGHOLE_2.5_PLATED | MOUNTINGHOLE2.5 | U$1 | m3 | 
| 12.7 | 0.0 | MOUNTINGHOLE_2.5_PLATED | MOUNTINGHOLE2.5 | U$2 | m3 |

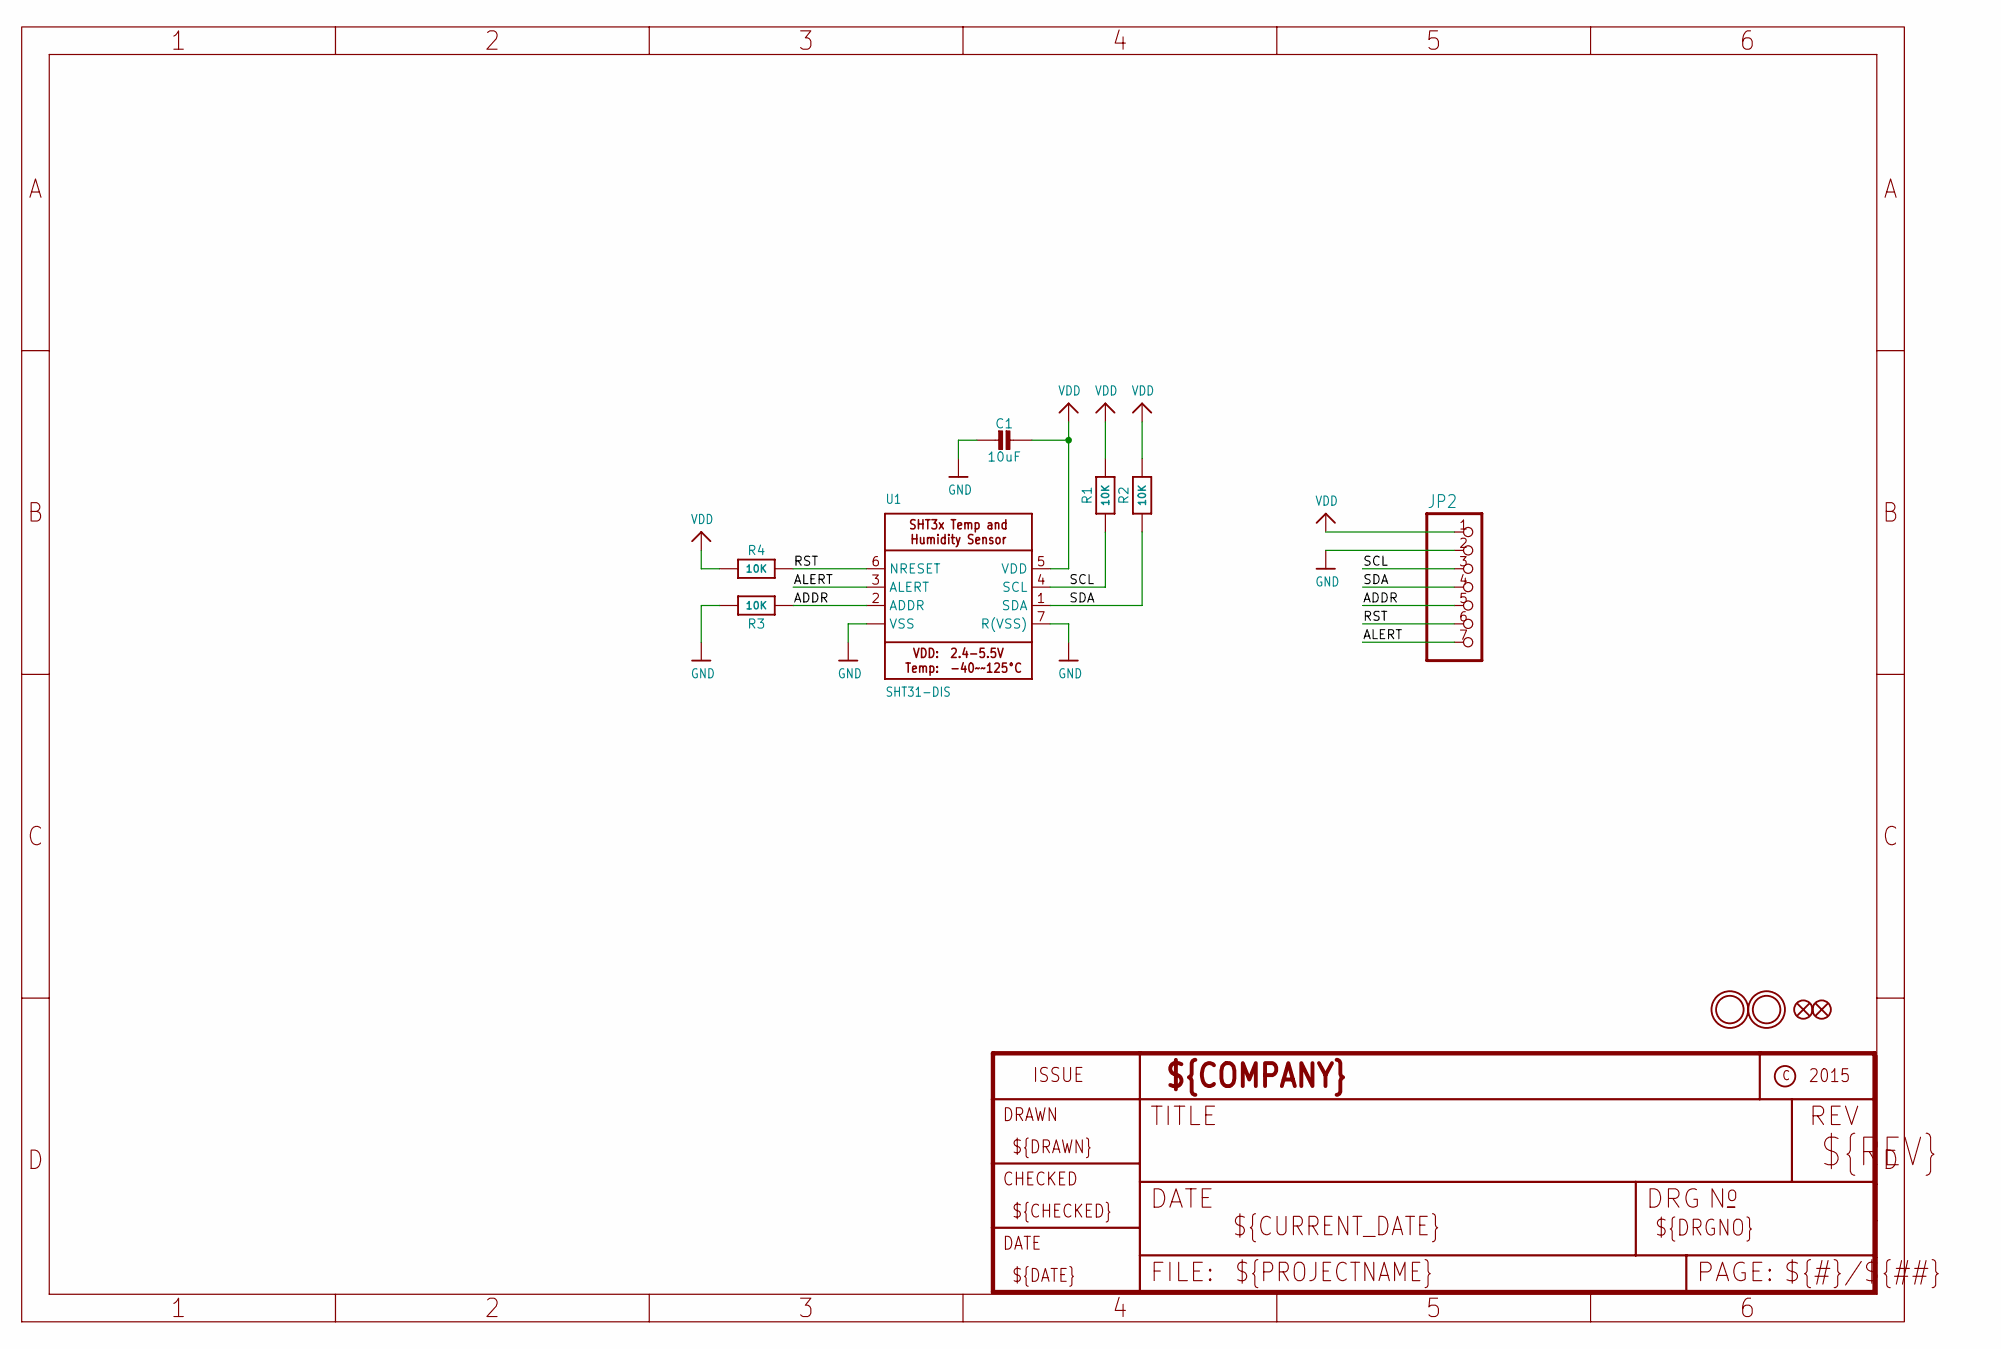
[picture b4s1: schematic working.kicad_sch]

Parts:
C1: 10uF; 0805-NO
FID2, FID3: FIDUCIAL""; FIDUCIAL_1MM
JP2: HEADER-1X770MIL; 1X07_ROUND_70
R1, R2, R4: 10K; 0805-NO
R3: 10K; _0805MP
U1: SHT31-DIS; SHT3X
U$1, U$2: MOUNTINGHOLE2.5; MOUNTINGHOLE_2.5_PLATED

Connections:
ADDR: JP2.5, R3.1, U1.2 (ADDR)
ALERT: JP2.7, U1.3 (ALERT)
GND: C1.2, JP2.2, R3.2, U1.7 (R(VSS)), U1.8 (VSS), U1.THERMAL (VSS)
RST: JP2.6, R4.2, U1.6 (NRESET)
SCL: JP2.3, R1.1, U1.4 (SCL)
SDA: JP2.4, R2.1, U1.1 (SDA)
VDD: C1.1, JP2.1, R1.2, R2.2, R4.1, U1.5 (VDD)

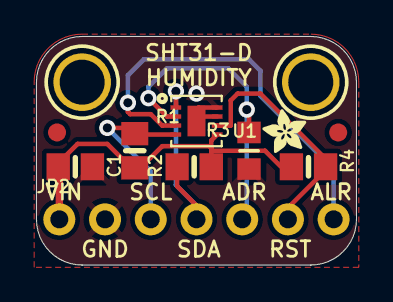
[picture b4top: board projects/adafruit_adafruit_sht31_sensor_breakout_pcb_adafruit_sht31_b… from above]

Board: 2 copper layers, 17.8 x 12.7 mm, 13 parts (1 on the bottom side), 7 nets.

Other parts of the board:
U$11: PCBFEAT-REV-040
U$13: ADAFRUIT_2.5MM
